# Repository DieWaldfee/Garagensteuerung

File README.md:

# Garagensteuerung
Steuerung eines Garagentorantriebs (Platine und Software) via Relaistrigger

### Beschreibung der Funktion:
Garagentorantriebe haben einen potentialfreien Relais-Kontakt. Wird dieser gebrückt, so wird der Antrieb aktiviert für eine Öffnen/Schließen -> das Tor fährt auf den nächsten Anschlag (oben oder unten). Wo das Tor aktuell steht und welche Richtung die Fahrt nehmen wird ist so nicht sensierbar.<br>
Im dazugekörigen blockly-Skript für ioBroker wird daher geprüft, welcher Endanschlag angefahren wird, um ggf. über einen weiteren Trigger (Triggerimpuls über das Relais) das Tor in die gewünschte Position zu bringen. Eine weitere Funktion ist - analog zu Rolladensteuerungen - eine Behanghöhe einzustellen. die wird über die Öffnungszeit / Schließzeit bestimmt -> 10% Behanghöhe entspricht damit 10% Öffnungszeit bis das Relais den Trigger zum stoppen des Torantriebs sendet- bzw. 90% Schließzeit, sollte das Tor am oberen Anschlag sein. (steht das Tor irgendwo, dann wird zuerst ein Anschlag angefahren, um dann den Behang einzustellen).

### Hardware:
Die Platine ist in dieser Version für eine Lochrasterplatine ausgelegt -> Leiterbahnen können mit einem Draht und Lötzinn erstellt werden. Dies ermöglicht es eigentlich jedem, der einen Lötkolben sein Eigen nennt es einfach nachzubauen :-) Die Eagle-Dateien liegen im Repository. Ein Überblick gibt das Fritzing-File. <br>
An der Platine können 4 Reed-Kontakte angeschlossen werden (oberer und unterer Anschlag, sowie zwei optionale Positionen). Über die Reedkontakte "Oben und Unten" wird die aktuelle Position des Tors bestimmt. Ein Relais dient dem Triggern des Garagenantriebs. Die STromversorgung kann entweder über ein Mini-Netzteil, oder einfach über ein USB-Netzteil realisiert werden (Letzteres ist bei mir im Einsatz). Drei LEDS zeigen ggf. Fehler, das Senden von MQTT-Botschaften und generell den Betrieb an. Optional kann ein DS18B20-Temperatursensor angeschlossen werden, sollte die Garagentemperatur von Interesse sein (weil der Wohnwagen dort steht, oder die Pflanzen überwintern sollen...).

### Software:
Der ESP32 benötigt natürlich seine Software. Das C++-File liegt im entsprechenden Verzeichnis und muss bezüglich MQTT-Broker-Account und Adresse angepasst werden. Zusätzlich ist natürlich auch das WiFi-Passwort und die IP-Adresse zu setzen. Danach kann das File z.B. mit der Arduino-IDE auf den ESP32DevKitV4-Modul aufgespielt werden. Compile und Upload brauchen nur ein paar Sekunden. Nach dem Start des ESP32 versucht der ESP32 den MQTT-Broker zu erreichen und übermittelt zyklisch den Status. Das angehängte blockly-Skript für den ioBroker liest die Botschaften aus und steuert das Tor an. Hier sind die Funktionen TorZu(um 23Uhr)... verortet. Der gesendete Torzustand kann im ioBroker zur Visualisierung verwendet werden. Ich steure den Telegramadapter an, sollte z.B. das Tor um 23Uhr nicht zu schließen sein (weil z.B. mein Sohn das Fahrad voll in den Fahrweg des Tores gestellt hat...).

### Abhängigkeiten:
OneWire.h:_____________OneWire by Jim Studt, Tom Pollard, Robin James... v2.3.8 (über Arduino IDE)<br>
DallasTemperature.h:___DallasTemperature by Miles Burton v4.0.3 (über Arduino IDE)<br>
WiFi.h:________________Arduino IDE<br>
WiFiClient.h:__________Arduino IDE<br>
PubSubClient.h:________PubSubClient by Nick O'Leary v2.8 (über Arduino IDE)<br>
esp_task_wdt.h:________Espressif IDE<br>

### Board ESP32
esp32 by Espressif Systems v1.0.6 (über Arduino IDE)<br>
Getestet habe ich auch v2.0.5<br>

### Benötigte Hardware:
* Relais <a href="https://www.amazon.de/gp/product/B0B5816YJ7/ref=ppx_yo_dt_b_search_asin_image?ie=UTF8&th=1"> Amazon </a> oder <a href="https://www.az-delivery.de/products/relais-modul"> AZ Delivery </a>
* ESP32 Dev Kit V4 <a href="https://www.azdelivery.de/products/esp-32-dev-kit-c-v4"> AZ Delivery </a>
* optional Temperatursensoren DS18B20 <a href="https://www.az-delivery.de/products/2er-set-ds18b20-mit-3m-kabel"> AZ Delivery </a>
* JST-Buchse <a href="https://www.amazon.de/gp/product/B0B2R99X99/ref=ppx_yo_dt_b_search_asin_title?ie=UTF8&psc=1"> Amazon </a>
* Klemmbuchse <a href="https://www.amazon.de/gp/product/B087RN8FDZ/ref=ppx_yo_dt_b_search_asin_title?ie=UTF8&th=1"> Amazon </a>
* Widerstände 4,7kOhm, 220 Ohm, 330 Ohm, Led grün, gelb und rot Amazon / eBay / Conrad...
* Levelshifter (3.3V <-> 5V)  <a href="https://www.amazon.de/RUNCCI-YUN-Pegelwandler-Converter-BiDirektional-Mikrocontroller/dp/B082F6BSB5/ref=sr_1_2?__mk_de_DE=%C3%85M%C3%85%C5%BD%C3%95%C3%91&crid=45TPZ9B8CUP9&keywords=level+shifter&qid=1699045033&sprefix=level+shifter%2Caps%2C103&sr=8-2"> Amazon </a>
* Reed-Kontakte <a href="https://www.amazon.de/schwarz-Sicherheitskontaktsensor-magnetischer-Reed-Schalter-T%C3%BCrsensor/dp/B07Z4NCWDD/ref=sr_1_3_sspa?__mk_de_DE=%C3%85M%C3%85%C5%BD%C3%95%C3%91&crid=39FKQI24X72OK&keywords=reedkontakt&qid=1703368970&sprefix=reedkontakt%2Caps%2C111&sr=8-3-spons&sp_csd=d2lkZ2V0TmFtZT1zcF9hdGY&th=1)"> Amazon </a>
* USB-Netzteil Amazon / eBay / Conrad...
* optional: Platinennetzteil AC-05-3    <a href="https://www.azdelivery.de/products/copy-of-220v-zu-5v-mini-netzteil"> AZ-Delivery </a>
* MC1490P (debouncer) auf Sockel, wenn gewünscht <a href="https://www.ebay.de/itm/201551880799?_trkparms=amclksrc%3DITM%26aid%3D1110006%26algo%3DHOMESPLICE.SIM%26ao%3D1%26asc%3D257778%26meid%3Db537b25c7a0745c29ea2a72120fca1d0%26pid%3D101195%26rk%3D5%26rkt%3D6%26sd%3D191674185616%26itm%3D201551880799%26pmt%3D1%26noa%3D0%26pg%3D4429486%26algv%3DSimPLWebV1EmbeddedAuctionsCPCAuto%26brand%3DBrand&_trksid=p4429486.c101195.m1851&amdata=cksum%3A201551880799b537b25c7a0745c29ea2a72120fca1d0%7Cenc%3AAQAIAAABAKQWTaSuKxcpq1j5hG%252Bz9F%252B8zK5%252FOpV48i2l8raehpQfSfTJViiimjfvkWmDgf%252BDpe3yyQwlK3DiDnYY85z1SxQJboT7HuhUjq4JgvlcaxtWrksoQQD9wDjrKbegZu4xYn3PZViDDDYymbWuHYvibUP57v0yaiUMN0YTUgeor4tEO0YIhs7PQ6%252BlbaxxWmKa98vDVPkxH4swvs1LeiFRFmmZbEV7QLNVZZrDm%252FVKXslR3RU%252FaKtNAYSS467lqopMuORWt353Z%252F97IyDlsTditsZk7nQ5%252BrWSFDjYWzKfd28Sj%252BQeszMJWaCxAHMu4uSDmqWne6J1qTMShVB5vi5c19k%253D%7Campid%3APL_CLK%7Cclp%3A4429486"> eBay </a>
* Kondensatoren <a href="https://www.amazon.de/AUKENIEN-Kondensator-Kondensatoren-Keramikkondensator-Kit/dp/B09NLZBC7R/ref=sr_1_1_sspa?__mk_de_DE=%C3%85M%C3%85%C5%BD%C3%95%C3%91&crid=HKCZID75QOX1&keywords=kondensator&qid=1703369261&sprefix=kondensator%2Caps%2C94&sr=8-1-spons&sp_csd=d2lkZ2V0TmFtZT1zcF9hdGY&th=1"> Amazon </a>

**Haftungsausschluss**<br>
Deutsch: Dieses Projekt arbeitet mit Netzspannung (220 V) und darf ausschließlich von qualifiziertem Fachpersonal aufgebaut, installiert und betrieben werden. Durch die anliegende Spannung besteht Lebensgefahr! Fehler in Schaltung oder Software können zu Sachschäden (z. B. an Gebäude oder Heizung) oder zu gefährlichen Situationen für Leib und Leben führen. Nutzung auf eigene Gefahr – jegliche Haftung wird ausgeschlossen.
<br>
English: This project operates with mains voltage (220 V) and must only be assembled, installed, and operated by qualified professionals. The present voltage poses a risk of fatal electric shock! Errors in circuitry or software may cause property damage (e.g., to buildings or heating systems) or create life-threatening situations. Use at your own risk – any liability is disclaimed.

<br>(Bezugslinks füge ich später noch hinzu)

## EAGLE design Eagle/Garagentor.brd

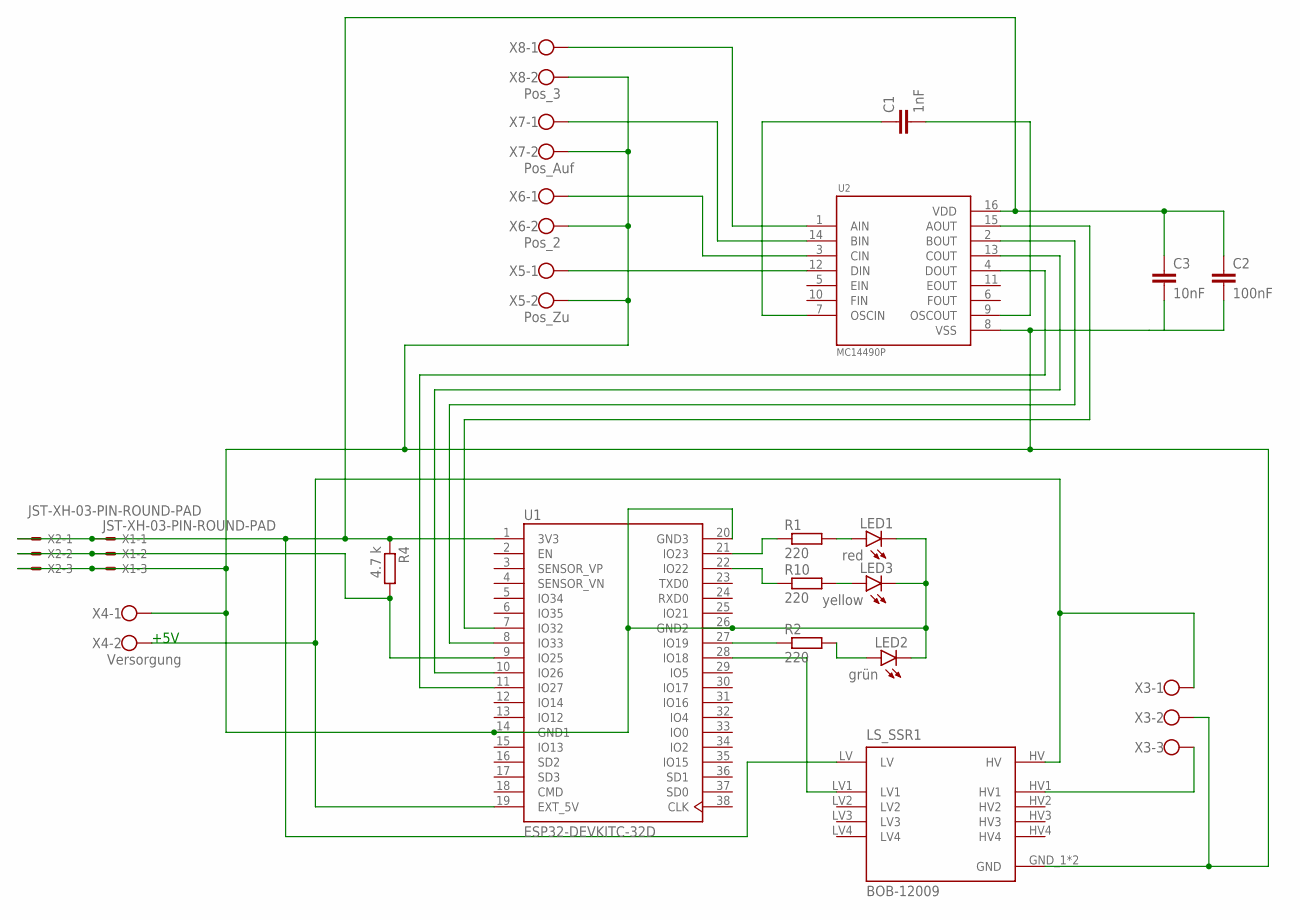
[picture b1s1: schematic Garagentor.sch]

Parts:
C1: 1nF; C050-024X044
C2: 100nF; C050-024X044
C3: 10nF; C050-024X044
LED1: red; LED3MM
LED2: grün; LED3MM
LED3: yellow; LED3MM
LS_SSR1: BOB-12009; CONV_BOB-12009
R1, R2, R10: 220; 0204/7
R4: 4.7 k; 0204/7
U1: ESP32-DEVKITC-32D; MODULE_ESP32-DEVKITC-32D
U2: MC14490P; DIP762W46P254L1918H444Q16P
X1, X2: JST-XH-03-PIN-ROUND-PAD; JST-XH-03-PACKAGE-ROUND-PAD
X3: W237-103
X4: Versorgung; W237-102
X5: Pos_Zu; W237-102
X6: Pos_2; W237-102
X7: Pos_Auf; W237-102
X8: Pos_3; W237-102

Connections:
GND$1: C2.2, C3.2, LED1.K (C), LED2.K (C), LED3.K (C), LS_SSR1.GND_1 (GND), LS_SSR1.GND_2 (GND), U1.14 (GND1), U1.20 (GND3), U1.26 (GND2), U2.8 (VSS), X1.3, X2.3, X3.2, X4.1, X5.2, X6.2, X7.2, X8.2
unnamed: R1.1, U1.21 (IO23)
unnamed: U1.7 (IO32), U2.15 (AOUT)
unnamed: R10.1, U1.22 (IO22)
unnamed: LED3.A, R10.2
unnamed: LS_SSR1.HV1, X3.3
unnamed: R2.1, U1.27 (IO19)
unnamed: LED1.A, R1.2
unnamed: LED2.A, R2.2
unnamed: U1.8 (IO33), U2.2 (BOUT)
unnamed: U1.10 (IO26), U2.13 (COUT)
unnamed: R4.2, U1.9 (IO25), X1.2, X2.2
unnamed: U1.11 (IO27), U2.4 (DOUT)
unnamed: U2.1 (AIN), X8.1
unnamed: U2.14 (BIN), X7.1
unnamed: U2.3 (CIN), X6.1
unnamed: LS_SSR1.LV1, U1.28 (IO18)
unnamed: U2.12 (DIN), X5.1
unnamed: C1.1, U2.7 (OSCIN)
unnamed: C1.2, U2.9 (OSCOUT)
VDD3$13: C2.1, C3.1, LS_SSR1.LV, R4.1, U1.1 (3V3), U2.16 (VDD), X1.1, X2.1
VDD5$3: LS_SSR1.HV, U1.19 (EXT_5V), X3.1, X4.2

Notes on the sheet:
+5V

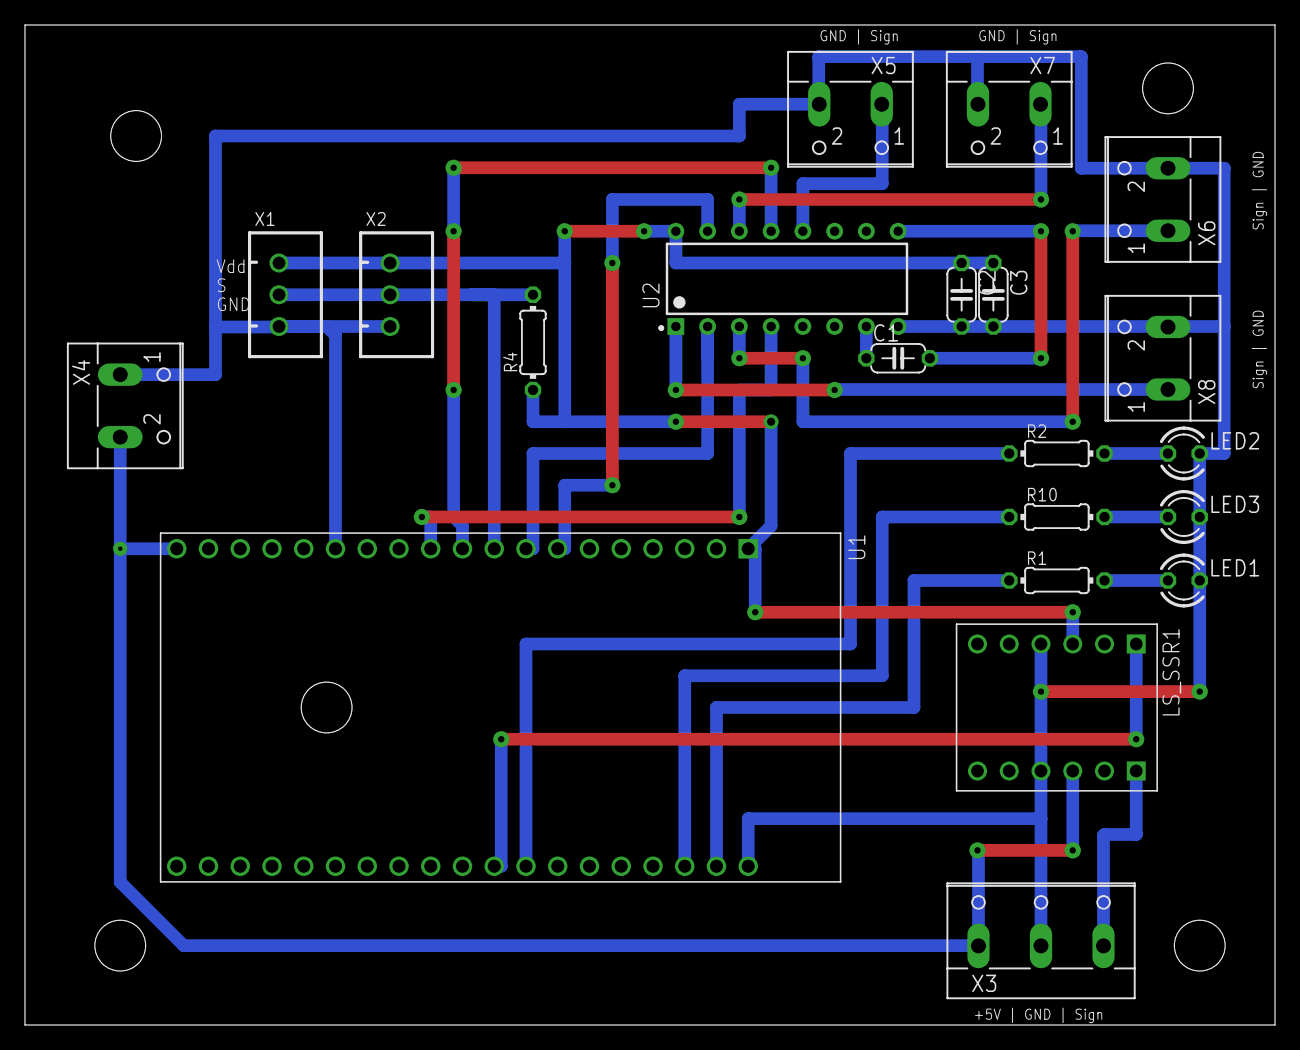
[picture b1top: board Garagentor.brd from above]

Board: 2 copper layers, 100.0 x 80.0 mm, 21 parts (0 on the bottom side), 22 nets.

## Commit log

2023-12-23 Update README.md
    erster commit
2023-12-23 Add files via upload
    ESP32 code hinzugefügt
2023-12-23 Add files via upload
    Fritzing hinzugefügt
2023-12-23 Add files via upload
    Eagle files hinzugefügt
2023-12-23 Add files via upload
    Eagle Library hinzugefügt
2023-12-23 Update README.md
    Beschreibung hinzugefügt
2023-12-23 Add files via upload
    Blockly-Skripte hinzugefügt
2023-12-23 Update README.md
    Optik der Überschriften
2023-12-23 Update README.md
    Optik erweitert
2023-12-23 Update README.md
    Links ergänzt
2024-05-13 Add files via upload
    Garagentorsteuerung V2.0
2024-07-19 V2.1 for new ESP API - watchdog updates, secret.h new
    watchdog handling is new -> fit to new spec.
    secrets.h separates login - informations and password
2025-05-29 V2.2 IP- and MAC-Adress output in state
    V2.2 IP- and MAC-Adress output in state
2025-09-13 MQTT communication queued & safeReset
    - MQTT communication is queued and controlled via task
    - safeReset to minimize broken data packages
2025-09-13 analog V2.4
2025-09-13 Bugfix MQTT reconnect
2026-05-03 code redesign & robustness
